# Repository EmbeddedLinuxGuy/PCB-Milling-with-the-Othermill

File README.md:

# PCB-Milling-with-the-Othermill

##Author: Kristof Aldenderfer
##TechShop San Francisco
Current version: 0.1

TODO:
* lots and lots

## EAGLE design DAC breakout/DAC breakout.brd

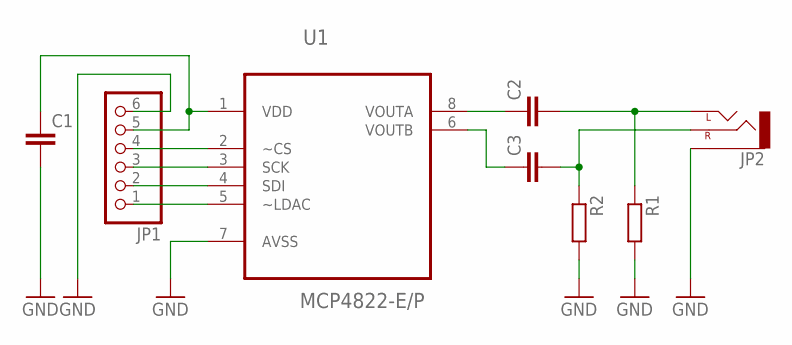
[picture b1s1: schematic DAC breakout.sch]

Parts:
C1, C2, C3: C5/3; C5B3
JP1: PINHD-1X6; 1X06
JP2: AUDIO-JACKPTH; AUDIO-JACK
R1, R2: R-EU_0204/7; 0204/7
U1: MCP4822-E/P; DIP254P762X432-8

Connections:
GND: C1.2, JP1.6, JP2.SLEEVE, R1.2, R2.2, U1.7 (AVSS)
unnamed: JP1.1, U1.5 (~LDAC)
unnamed: JP1.2, U1.4 (SDI)
unnamed: JP1.3, U1.3 (SCK)
unnamed: JP1.4, U1.2 (~CS)
unnamed: C1.1, JP1.5, U1.1 (VDD)
unnamed: C3.2, JP2.RING (RIGHT), R2.1
unnamed: C2.1, U1.8 (VOUTA)
unnamed: C3.1, U1.6 (VOUTB)
unnamed: C2.2, JP2.TIP (LEFT), R1.1

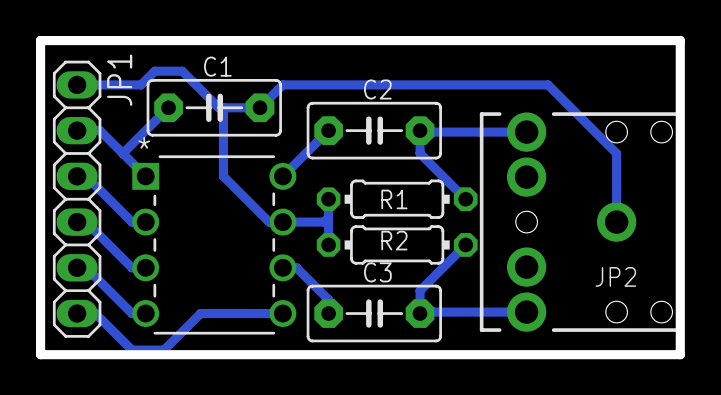
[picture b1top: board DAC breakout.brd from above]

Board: 2 copper layers, 35.5 x 17.4 mm, 8 parts (0 on the bottom side), 10 nets.

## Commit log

2015-12-09 Version 0.1
    Added sch, brd, and first iteration of packet
2015-12-10 generate gcode from gerber

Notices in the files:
parts and their libraries:
SparkFun-Connectors: Licensing: Creative Commons ShareAlike 4.0 International - https://creativecommons.org/licenses/by-sa/4.0
